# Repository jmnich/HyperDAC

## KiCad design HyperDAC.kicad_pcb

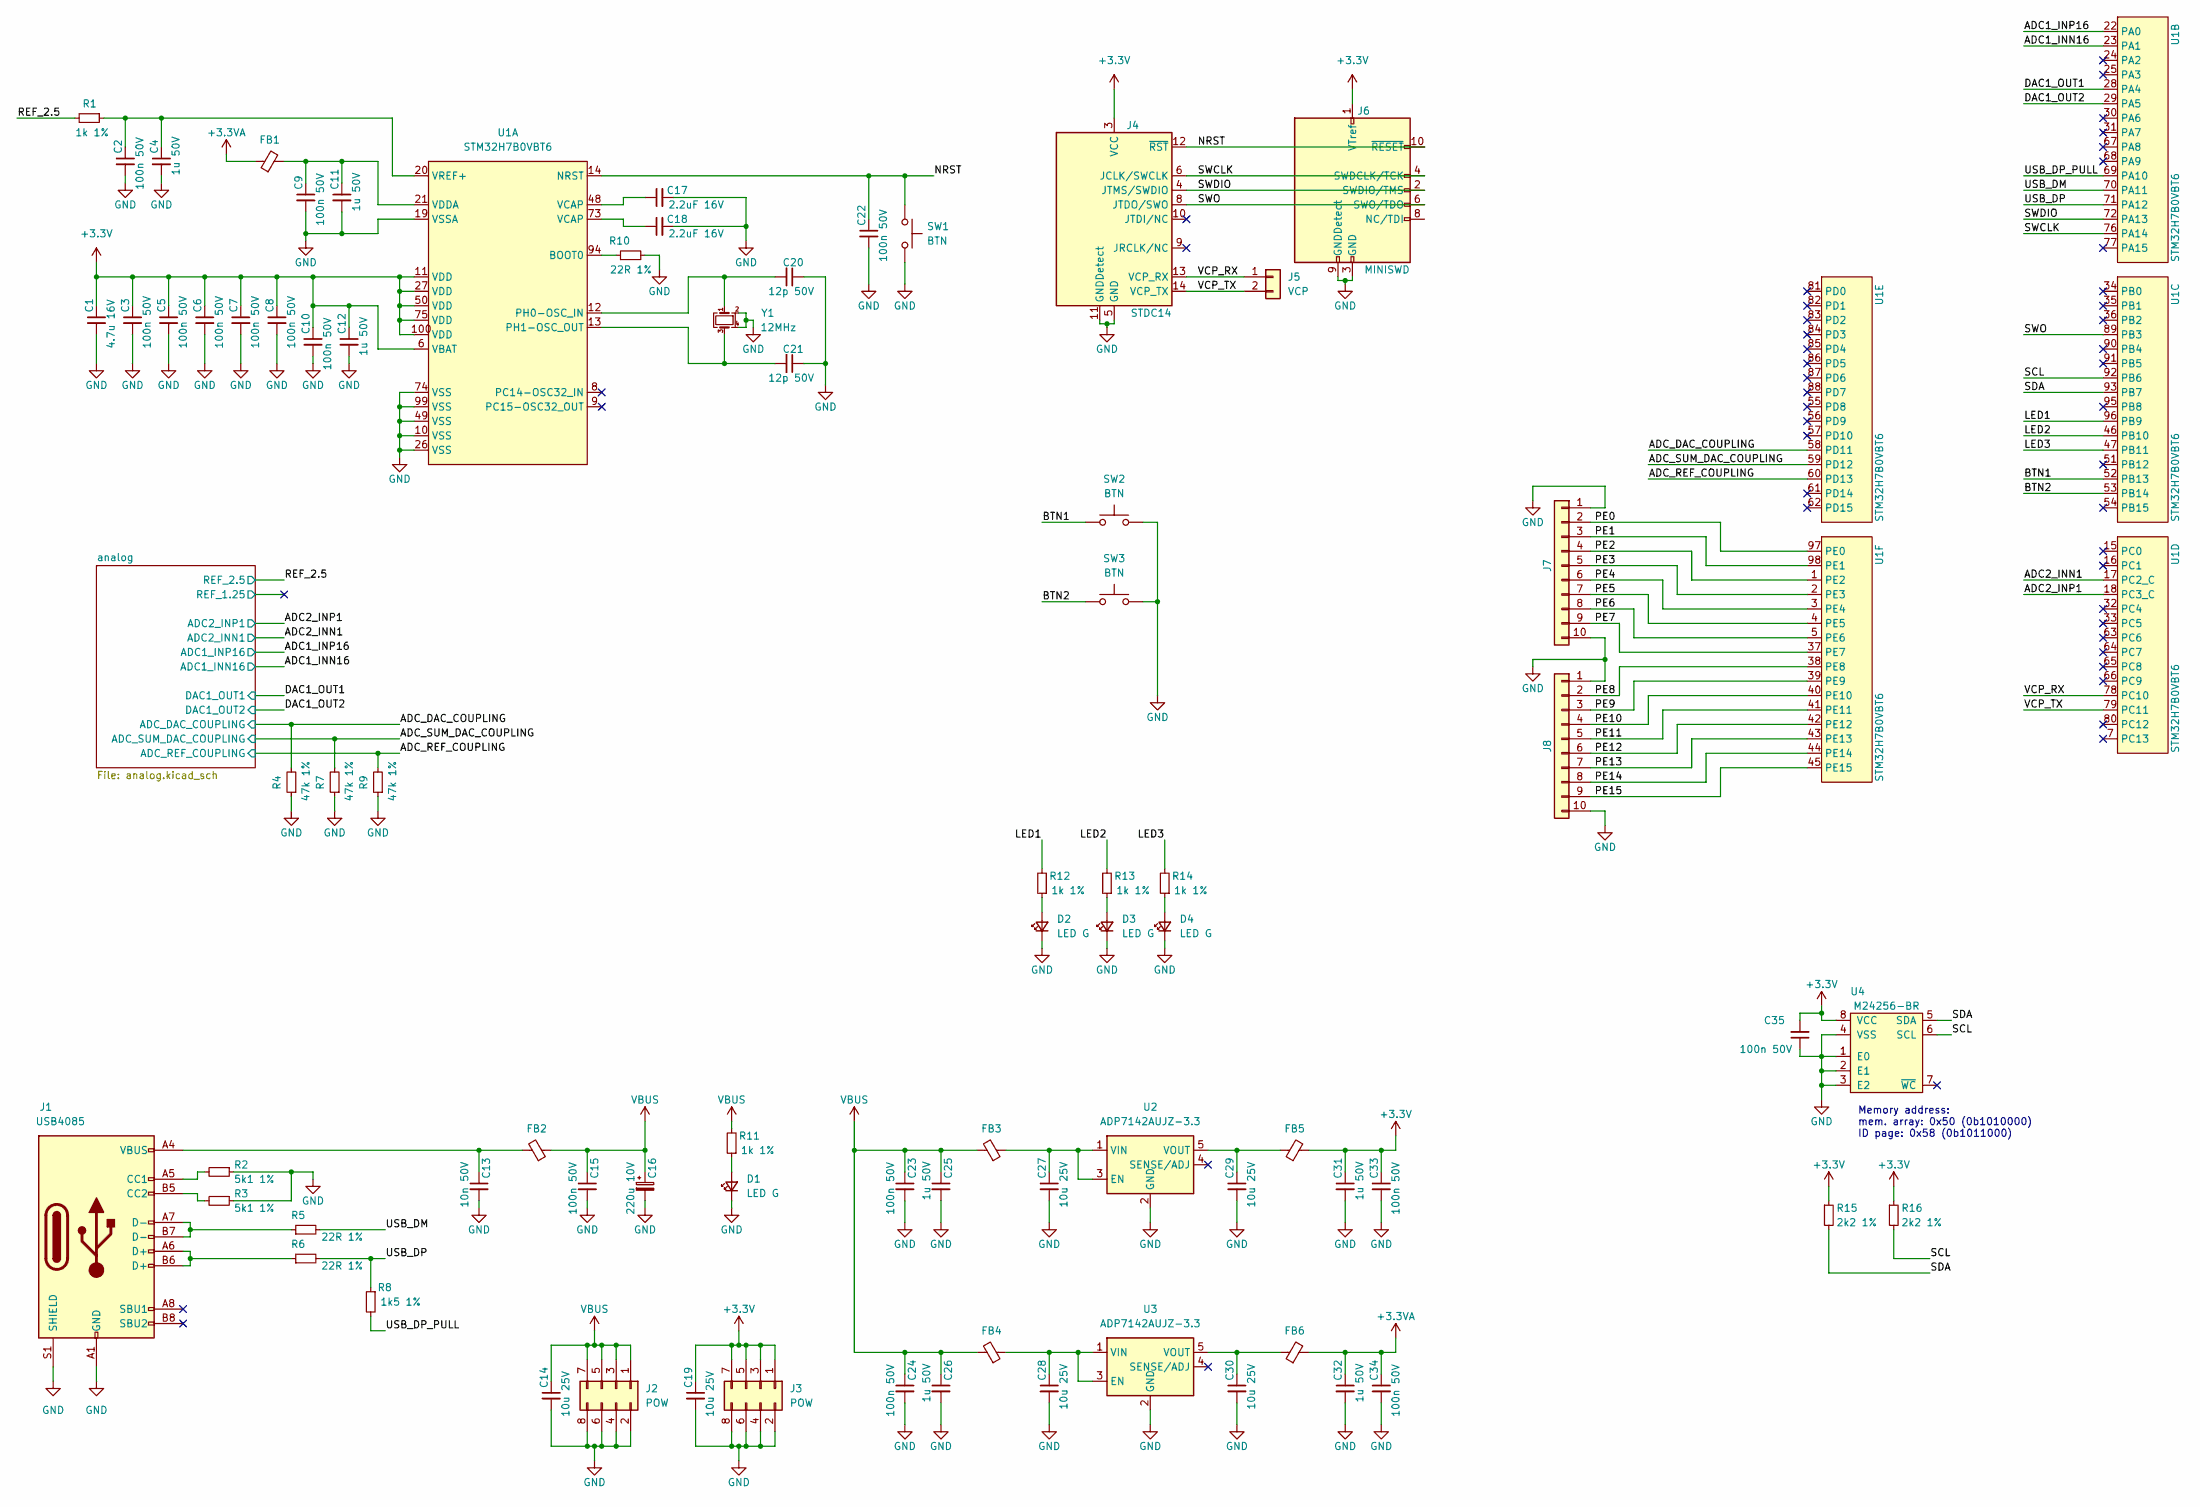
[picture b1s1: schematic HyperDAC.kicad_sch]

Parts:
C1: 4.7u 16V; C_0603_1608Metric_Pad1.08x0.95mm_HandSolder; jlc C19666
C2, C3, C5, C6, C7, C8, C9, C10, C15, C22, C23, C24, C33, C34: 100n 50V; C_0603_1608Metric_Pad1.08x0.95mm_HandSolder; jlc C14663
C4, C11, C12, C25, C26, C31, C32: 1u 50V; C_0603_1608Metric_Pad1.08x0.95mm_HandSolder; jlc C15849
C13: 10n 50V; C_0603_1608Metric; jlc C57112
C14, C19, C27, C28, C29, C30: 10u 25V; C_0805_2012Metric_Pad1.18x1.45mm_HandSolder; jlc C15850
C16: 220u 10V; CP_Elec_6.3x7.7; jlc C249876
C17, C18: 2.2uF 16V; C_0603_1608Metric_Pad1.08x0.95mm_HandSolder; jlc C23630
C20, C21: 12p 50V; C_0603_1608Metric_Pad1.08x0.95mm_HandSolder; jlc C38523
C35: 100n 50V; C_0603_1608Metric; jlc C14663
D1, D2, D3, D4: LED G; LED_0603_1608Metric_Pad1.05x0.95mm_HandSolder; jlc C72043
FB1: 600R 100MHz; L_0805_2012Metric_Pad1.05x1.20mm_HandSolder; jlc C1017
FB2, FB3, FB4, FB5, FB6: 100R 100MHz; L_0805_2012Metric_Pad1.05x1.20mm_HandSolder; jlc C1015
J1: USB4085; USB_C_Receptacle_GCT_USB4085; MPN USB4085
J2, J3: POW; PinHeader_2x04_P2.54mm_Vertical; jlc C5156676
J4: STDC14; PinHeader_2x07_P1.27mm_Vertical_SMD; jlc C3975190
J5: VCP; PinHeader_1x02_P2.54mm_Vertical
J6: MINISWD; 10pin_1.27_socket
J7, J8: Conn_01x10; PinHeader_1x10_P2.54mm_Vertical; jlc C57369
R1, R11, R12, R13, R14: 1k 1%; R_0603_1608Metric_Pad0.98x0.95mm_HandSolder; jlc C21190
R2, R3: 5k1 1%; R_0603_1608Metric_Pad0.98x0.95mm_HandSolder; jlc C23186
R4, R7, R9: 47k 1%; R_0603_1608Metric_Pad0.98x0.95mm_HandSolder; jlc C25819
R5, R6, R10: 22R 1%; R_0603_1608Metric_Pad0.98x0.95mm_HandSolder; jlc C23345
R8: 1k5 1%; R_0603_1608Metric_Pad0.98x0.95mm_HandSolder; jlc C22843
R15, R16: 2k2 1%; R_0603_1608Metric; jlc C4190
SW1, SW2, SW3: BTN; SW_SPST_B3SL-1022P; jlc C318884
U1: STM32H7B0VBT6; LQFP-100_14x14mm_P0.5mm; MPN STM32H7B0VBT6; jlc C730227
U2, U3: ADP7142AUJZ-3.3; TSOT-23-5; jlc C208543
U4: M24256-BR; SOIC-8_3.9x4.9mm_P1.27mm; MPN M24256-BR; jlc C79984
Y1: 12MHz; Crystal_SMD_3225-4Pin_3.2x2.5mm; MPN X322512MSB4SI; jlc C9002

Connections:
+3.3VA: C32.1, C34.1, FB1.1, FB6.2; also elsewhere on the board
+3V3: C1.1, C3.1, C5.1, C6.1, C7.1, C8.1, C10.1, C12.1, C19.1, C31.1, C33.1, C35.2, FB5.2, J3.1, J3.3, J3.5, J3.7, J4.3 (VCC), J6.1 (VTref), R15.1, R16.1, U1.6 (VBAT), U1.11 (VDD), U1.27 (VDD), U1.50 (VDD), U1.75 (VDD), U1.100 (VDD), U4.8 (VCC)
/ADC1_INN16: U1.23 (PA1); also elsewhere on the board
/ADC1_INP16: U1.22 (PA0); also elsewhere on the board
/ADC2_INN1: U1.17 (PC2_C); also elsewhere on the board
/ADC2_INP1: U1.18 (PC3_C); also elsewhere on the board
/ADC_DAC_COUPLING: R4.2, U1.58 (PD11); also elsewhere on the board
/ADC_REF_COUPLING: R9.2, U1.60 (PD13); also elsewhere on the board
/ADC_SUM_DAC_COUPLING: R7.2, U1.59 (PD12); also elsewhere on the board
/BTN1: SW2.1, U1.52 (PB13)
/BTN2: SW3.1, U1.53 (PB14)
/DAC1_OUT1: U1.28 (PA4); also elsewhere on the board
/DAC1_OUT2: U1.29 (PA5); also elsewhere on the board
/LED1: R12.2, U1.96 (PB9)
/LED2: R13.2, U1.46 (PB10)
/LED3: R14.2, U1.47 (PB11)
/NRST: C22.1, J4.12 (~RST), J6.10 (~RESET), SW1.1, U1.14 (NRST)
/PE0: J7.2, U1.97 (PE0)
/PE1: J7.3, U1.98 (PE1)
/PE2: J7.4, U1.1 (PE2)
/PE3: J7.5, U1.2 (PE3)
/PE4: J7.6, U1.3 (PE4)
/PE5: J7.7, U1.4 (PE5)
/PE6: J7.8, U1.5 (PE6)
/PE7: J7.9, U1.37 (PE7)
/PE8: J8.2, U1.38 (PE8)
/PE9: J8.3, U1.39 (PE9)
/PE10: J8.4, U1.40 (PE10)
/PE11: J8.5, U1.41 (PE11)
/PE12: J8.6, U1.42 (PE12)
/PE13: J8.7, U1.43 (PE13)
/PE14: J8.8, U1.44 (PE14)
/PE15: J8.9, U1.45 (PE15)
/REF_2.5: R1.2; also elsewhere on the board
/SCL: R16.2, U1.92 (PB6), U4.6 (SCL)
/SDA: R15.2, U1.93 (PB7), U4.5 (SDA)
/SWCLK: J4.6 (JCLK/SWCLK), J6.4 (SWDCLK/TCK), U1.76 (PA14)
/SWDIO: J4.4 (JTMS/SWDIO), J6.2 (SWDIO/TMS), U1.72 (PA13)
/SWO: J4.8 (JTDO/SWO), J6.6 (SWO/TDO), U1.89 (PB3)
/USB_DM: R5.2, U1.70 (PA11)
/USB_DP: R6.2, R8.1, U1.71 (PA12)
/USB_DP_PULL: R8.2, U1.69 (PA10)
/VCP_RX: J4.13 (VCP_RX), J5.1, U1.78 (PC10)
/VCP_TX: J4.14 (VCP_TX), J5.2, U1.79 (PC11)
GND: C1.2, C2.2, C3.2, C4.2, C5.2, C6.2, C7.2, C8.2, C9.2, C10.2, C11.2, C12.2, C13.2, C14.2, C15.2, C16.2, C17.2, C18.2, C19.2, C20.1, C21.1, C22.2, C23.2, C24.2, C25.2, C26.2, C27.2, C28.2, C29.2, C30.2, C31.2, C32.2, C33.2, C34.2, C35.1, D1.1 (K), D2.1 (K), D3.1 (K), D4.1 (K), J1.A1 (GND), J1.A12 (GND), J1.B1 (GND), J1.B12 (GND), J1.S1 (SHIELD), J2.2, J2.4, J2.6, J2.8, J3.2, J3.4, J3.6, J3.8, J4.5 (GND), J4.7 (GND), J4.11 (GNDDetect), J6.3 (GND), J6.5 (GND), J6.9 (GNDDetect), J7.1, J7.10, J8.1, J8.10, R2.1, R3.1, R4.1, R7.1, R9.1, R10.2, SW1.2, SW2.2, SW3.2, U1.10 (VSS), U1.19 (VSSA), U1.26 (VSS), U1.49 (VSS), U1.74 (VSS), U1.99 (VSS), U2.2 (GND), U3.2 (GND), U4.1 (E0), U4.2 (E1), U4.3 (E2), U4.4 (VSS), Y1.2, Y1.4; also elsewhere on the board
unnamed: C2.1, C4.1, R1.1, U1.20 (VREF+)
unnamed: C9.1, C11.1, FB1.2, U1.21 (VDDA)
unnamed: C13.1, FB2.2, J1.A4 (VBUS), J1.A9 (VBUS), J1.B4 (VBUS), J1.B9 (VBUS)
unnamed: C17.1, U1.48 (VCAP)
unnamed: C18.1, U1.73 (VCAP)
unnamed: C20.2, U1.12 (PH0-OSC_IN), Y1.1
unnamed: C21.2, U1.13 (PH1-OSC_OUT), Y1.3
unnamed: C27.1, FB3.1, U2.1 (VIN), U2.3 (EN)
unnamed: C28.1, FB4.1, U3.1 (VIN), U3.3 (EN)
unnamed: C29.1, FB5.1, U2.5 (VOUT)
unnamed: C30.1, FB6.1, U3.5 (VOUT)
unnamed: D1.2 (A), R11.1
unnamed: D2.2 (A), R12.1
unnamed: D3.2 (A), R13.1
unnamed: D4.2 (A), R14.1
unnamed: J1.A5 (CC1), R2.2
unnamed: J1.A6 (D+), J1.B6 (D+), R6.1
unnamed: J1.A7 (D-), J1.B7 (D-), R5.1
unnamed: J1.B5 (CC2), R3.2
unnamed: R10.1, U1.94 (BOOT0)
VBUS: C14.1, C15.1, C16.1, C23.1, C24.1, C25.1, C26.1, FB2.1, FB3.2, FB4.2, J2.1, J2.3, J2.5, J2.7, R11.2

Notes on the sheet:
Memory address: mem. array: 0x50 (0b1010000) ID page: 0x58 (0b1011000)

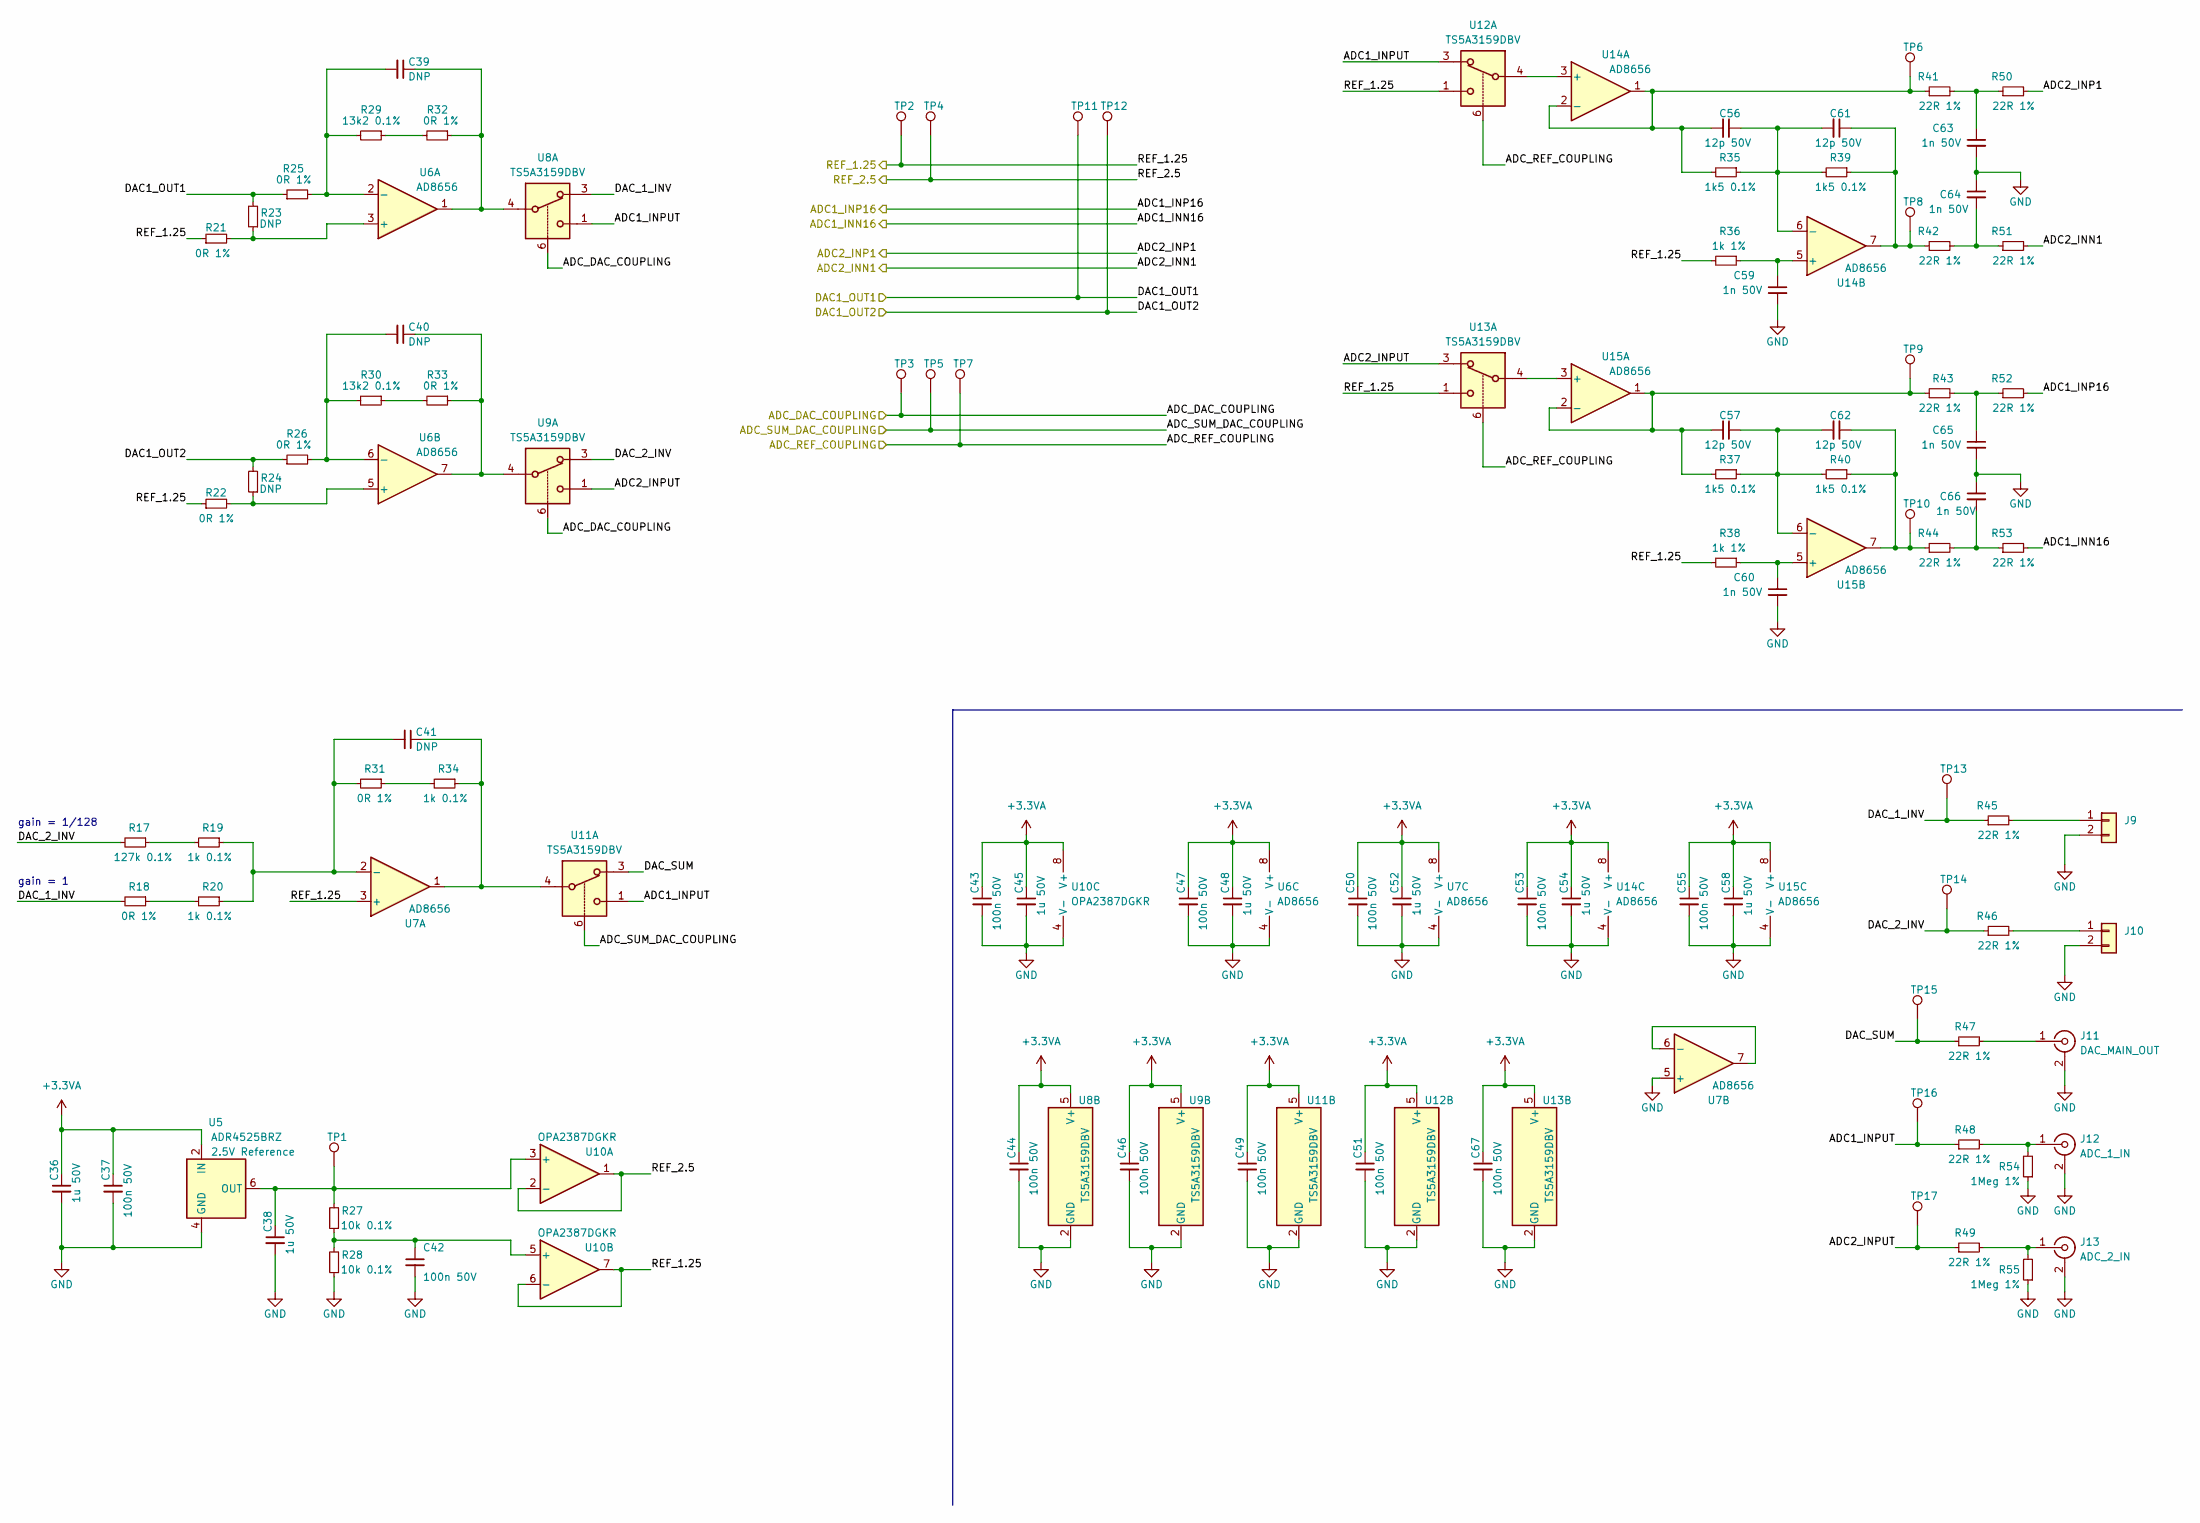
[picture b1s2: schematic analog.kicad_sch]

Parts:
C36, C38, C45, C48, C52, C54, C58: 1u 50V; C_0603_1608Metric_Pad1.08x0.95mm_HandSolder; jlc C15849
C37, C42, C43, C44, C46, C47, C49, C50, C51, C53, C55, C67: 100n 50V; C_0603_1608Metric_Pad1.08x0.95mm_HandSolder; jlc C14663
C39, C40, C41: DNP; C_0603_1608Metric_Pad1.08x0.95mm_HandSolder
C56, C57, C61, C62: 12p 50V; C_0603_1608Metric_Pad1.08x0.95mm_HandSolder; jlc C38523
C59, C60, C63, C64, C65, C66: 1n 50V; C_0603_1608Metric_Pad1.08x0.95mm_HandSolder; jlc C1588
J9, J10: Conn_01x02; PinHeader_1x02_P2.54mm_Vertical
J11: DAC_MAIN_OUT; 1-1634613-0; jlc C709673
J12: ADC_1_IN; 1-1634613-0; jlc C709673
J13: ADC_2_IN; 1-1634613-0; jlc C709673
R17: 127k 0.1%; R_0603_1608Metric_Pad0.98x0.95mm_HandSolder; jlc C705722
R18, R21, R22, R25, R26, R31, R32, R33: 0R 1%; R_0603_1608Metric_Pad0.98x0.95mm_HandSolder; jlc C21189
R19, R20, R34: 1k 0.1%; R_0603_1608Metric_Pad0.98x0.95mm_HandSolder; jlc C412384
R23, R24: DNP; R_0603_1608Metric_Pad0.98x0.95mm_HandSolder
R27, R28: 10k 0.1%; R_0603_1608Metric_Pad0.98x0.95mm_HandSolder; jlc C844890
R29, R30: 13k2 0.1%; R_0603_1608Metric_Pad0.98x0.95mm_HandSolder; jlc C861116
R35, R37, R39, R40: 1k5 0.1%; R_0603_1608Metric_Pad0.98x0.95mm_HandSolder; jlc C844455
R36, R38: 1k 1%; R_0603_1608Metric_Pad0.98x0.95mm_HandSolder; jlc C21190
R41, R42, R43, R44, R45, R46, R47, R48, R49, R50, R51, R52, R53: 22R 1%; R_0603_1608Metric_Pad0.98x0.95mm_HandSolder; jlc C23345
R54, R55: 1Meg 1%; R_0603_1608Metric_Pad0.98x0.95mm_HandSolder; jlc C22935
TP1, TP2, TP3, TP4, TP5, TP6, TP7, TP8, TP9, TP10, TP11, TP12, TP13, TP14, TP15, TP16, TP17: TestPoint; TestPoint_Pad_D2.0mm
U5: ADR4525BRZ; SOIC-8_3.9x4.9mm_P1.27mm; jlc C403914
U6, U7, U14, U15: AD8656; MSOP-8_3x3mm_P0.65mm; MPN AD8656ARMZ; jlc C208582
U8, U9, U11, U12, U13: TS5A3159DBV; SOT-23-6; jlc C92485
U10: OPA2387DGKR; VSSOP-8_3.0x3.0mm_P0.65mm; MPN OPA2387DGKR; jlc C2861203

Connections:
+3.3VA: C36.1, C37.1, C43.1, C44.1, C45.1, C46.1, C47.1, C48.1, C49.1, C50.1, C51.1, C52.1, C53.1, C54.1, C55.1, C58.1, C67.1, U5.2 (IN), U6.8 (V+), U7.8 (V+), U8.5 (V+), U9.5 (V+), U10.8 (V+), U11.5 (V+), U12.5 (V+), U13.5 (V+), U14.8 (V+), U15.8 (V+); also elsewhere on the board
/ADC1_INN16: R53.2; also elsewhere on the board
/ADC1_INP16: R52.2; also elsewhere on the board
/ADC2_INN1: R51.2; also elsewhere on the board
/ADC2_INP1: R50.2; also elsewhere on the board
/ADC_DAC_COUPLING: TP3.1, U8.6, U9.6; also elsewhere on the board
/ADC_REF_COUPLING: TP7.1, U12.6, U13.6; also elsewhere on the board
/ADC_SUM_DAC_COUPLING: TP5.1, U11.6; also elsewhere on the board
/DAC1_OUT1: R23.2, R25.1, TP11.1; also elsewhere on the board
/DAC1_OUT2: R24.2, R26.1, TP12.1; also elsewhere on the board
/REF_2.5: TP4.1, U10.1, U10.2 (-); also elsewhere on the board
/analog/ADC1_INPUT: R48.1, TP16.1, U8.1, U11.1, U12.3
/analog/ADC2_INPUT: R49.1, TP17.1, U9.1, U13.3
/analog/DAC_1_INV: R18.2, R45.1, TP13.1, U8.3
/analog/DAC_2_INV: R17.2, R46.1, TP14.1, U9.3
/analog/DAC_SUM: R47.1, TP15.1, U11.3
/analog/REF_1.25: R21.1, R22.1, R36.2, R38.2, TP2.1, U7.3 (+), U10.6 (-), U10.7, U12.1, U13.1
GND: C36.2, C37.2, C38.2, C42.2, C43.2, C44.2, C45.2, C46.2, C47.2, C48.2, C49.2, C50.2, C51.2, C52.2, C53.2, C54.2, C55.2, C58.2, C59.2, C60.2, C63.2, C64.1, C65.2, C66.1, C67.2, J9.2, J10.2, J11.2 (Ext), J12.2 (Ext), J13.2 (Ext), R28.1, R54.1, R55.1, U5.4 (GND), U6.4 (V-), U7.4 (V-), U7.5 (+), U8.2 (GND), U9.2 (GND), U10.4 (V-), U11.2 (GND), U12.2 (GND), U13.2 (GND), U14.4 (V-), U15.4 (V-); also elsewhere on the board
unnamed: C38.1, R27.2, TP1.1, U5.6 (OUT), U10.3 (+)
unnamed: C39.1, R32.1, U6.1, U8.4
unnamed: C39.2, R25.2, R29.2, U6.2 (-)
unnamed: C40.1, R33.1, U6.7, U9.4
unnamed: C40.2, R26.2, R30.2, U6.6 (-)
unnamed: C41.1, R34.1, U7.1, U11.4
unnamed: C41.2, R19.1, R20.1, R31.2, U7.2 (-)
unnamed: C42.1, R27.1, R28.2, U10.5 (+)
unnamed: C56.1, C61.2, R35.1, R39.2, U14.6 (-)
unnamed: C56.2, R35.2, R41.1, TP6.1, U14.1, U14.2 (-)
unnamed: C57.1, C62.2, R37.1, R40.2, U15.6 (-)
unnamed: C57.2, R37.2, R43.1, TP9.1, U15.1, U15.2 (-)
unnamed: C59.1, R36.1, U14.5 (+)
unnamed: C60.1, R38.1, U15.5 (+)
unnamed: C61.1, R39.1, R42.1, TP8.1, U14.7
unnamed: C62.1, R40.1, R44.1, TP10.1, U15.7
unnamed: C63.1, R41.2, R50.1
unnamed: C64.2, R42.2, R51.1
unnamed: C65.1, R43.2, R52.1
unnamed: C66.2, R44.2, R53.1
unnamed: J9.1, R45.2
unnamed: J10.1, R46.2
unnamed: J11.1 (In), R47.2
unnamed: J12.1 (In), R48.2, R54.2
unnamed: J13.1 (In), R49.2, R55.2
unnamed: R17.1, R19.2
unnamed: R18.1, R20.2
unnamed: R21.2, R23.1, U6.3 (+)
unnamed: R22.2, R24.1, U6.5 (+)
unnamed: R29.1, R32.2
unnamed: R30.1, R33.2
unnamed: R31.1, R34.2
unnamed: U7.6 (-), U7.7
unnamed: U12.4, U14.3 (+)
unnamed: U13.4, U15.3 (+)

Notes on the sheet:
gain = 1
gain = 1/128

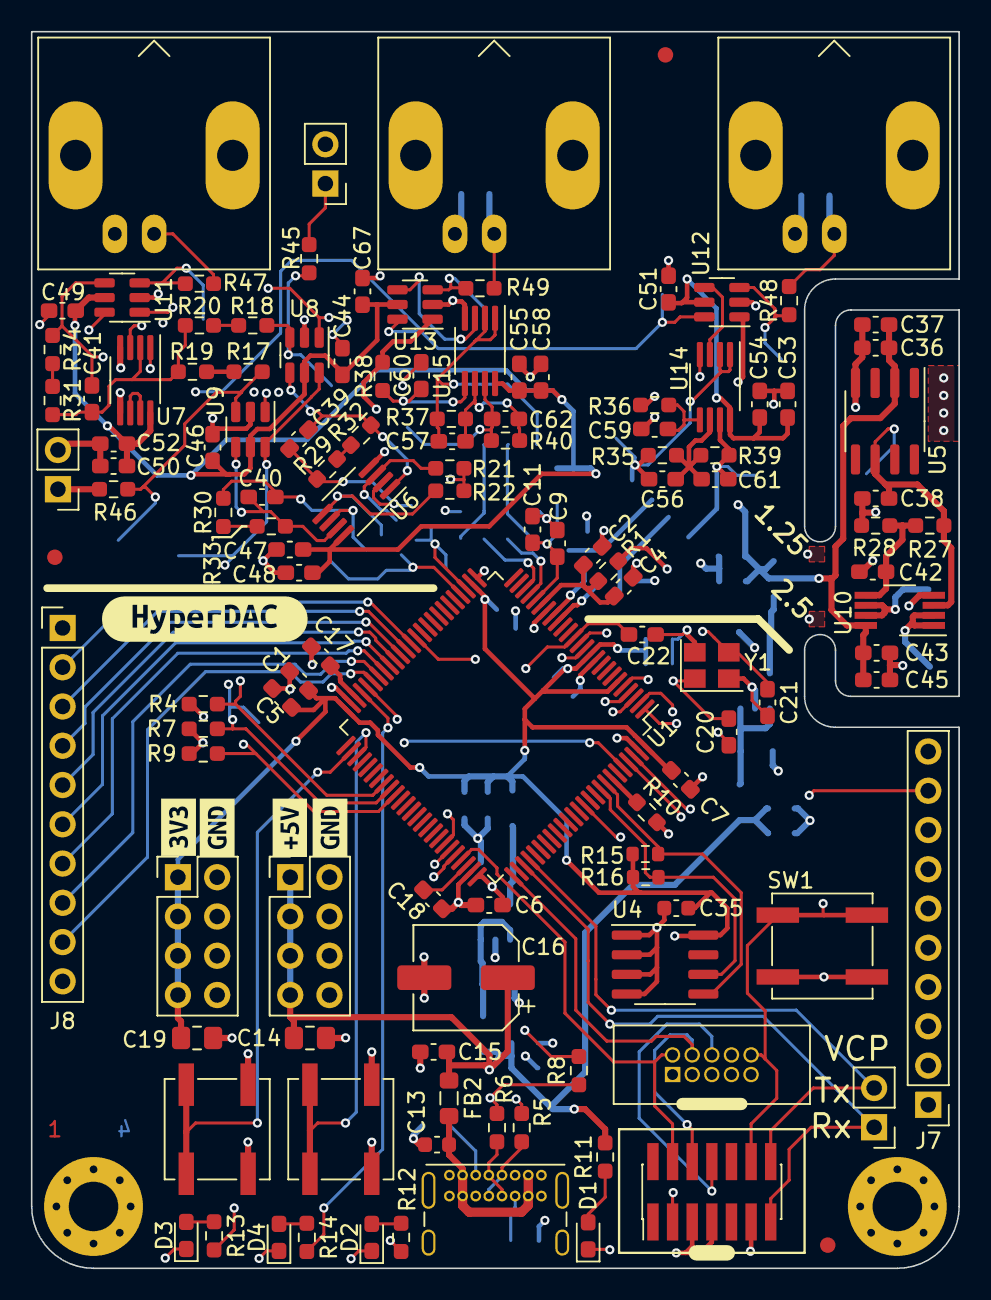
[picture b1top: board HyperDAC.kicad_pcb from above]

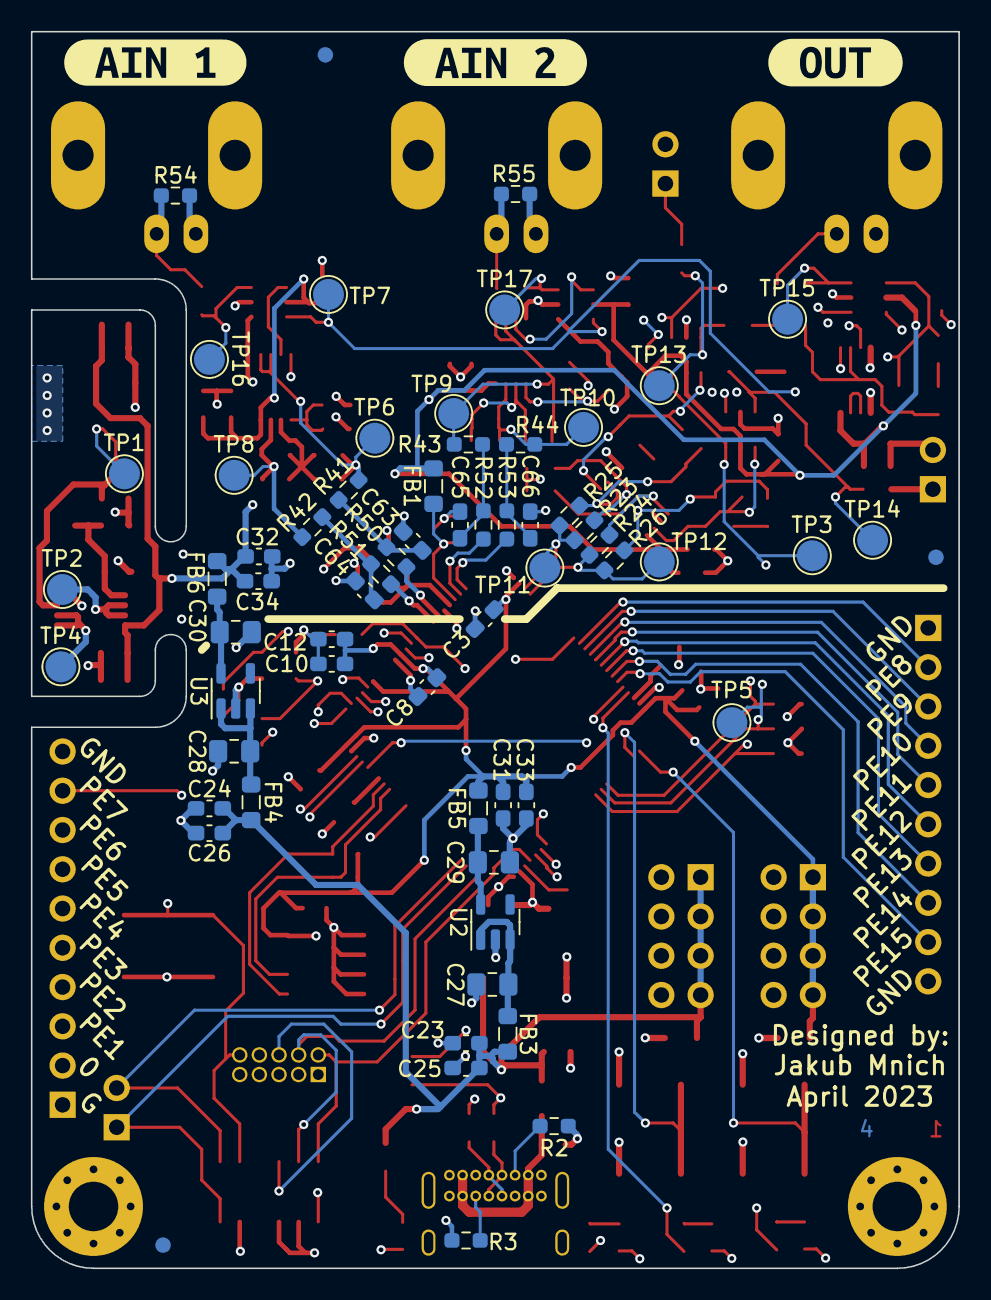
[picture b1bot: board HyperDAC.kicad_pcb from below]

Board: 4 copper layers, 60.0 x 80.0 mm, 189 parts (63 on the bottom side), 107 nets.

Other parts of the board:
kibuzzard-6440F6E9: G***; kibuzzard-6440F6E9
kibuzzard-6440F78E, kibuzzard-6440F78E#2: G***; kibuzzard-6440F78E
kibuzzard-6440F79B: G***; kibuzzard-6440F79B
kibuzzard-6440F782: G***; kibuzzard-6440F782
kibuzzard-6441254C: G***; kibuzzard-6441254C
kibuzzard-64412532: G***; kibuzzard-64412532
kibuzzard-64412543: G***; kibuzzard-64412543

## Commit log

2023-04-18 repo init
2023-04-19 sch done
2023-04-19 routing in progress
2023-04-20 Production ready
